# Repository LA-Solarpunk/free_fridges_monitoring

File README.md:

# Free Fridge Monitoring

The city of LA has a network of [free community fridges](https://www.lacommunityfridges.com/)
that serve as distributed food pantries for the city. The [K-Town fridge](https://www.lacommunityfridges.com/fridge/koreatown-solar/r/recZlfyUDA3hGEN5D) is a solar powered version. We're working with
the solar fridge group to build a remote monitoring system for them.

A cloudy week or a door left ajar can spoil everything inside before anyone
notices. This system reports temperature, door state, and battery charge from each
fridge to a central server.

## How it works

A Raspberry Pi at each fridge reads its sensors and publishes a JSON reading once a
minute over MQTT. The Pi reaches the server over Tailscale, so no fridge needs a public
IP or a port forward.

```
Fridge Pi ──> MQTT over Tailscale──> Mosquitto ──> Telegraf ──> InfluxDB
```

Mosquitto is the broker. Telegraf subscribes to `fridges/sensor_data`, parses the JSON,
and writes points into the `freefridges` bucket in InfluxDB. Each fridge has its own
broker account and ACL entry, so a stolen Pi can only publish as itself.

There is a second topic, `fridges/alerts`, that fridges are permitted to write to.
Nothing consumes it yet.

## Server setup

See [ServerConfig/README.md](ServerConfig/README.md). That covers Tailscale, the three
services, and adding a broker account for a new fridge.

## Fridge setup

### 1. Operating system

Flash Raspberry Pi OS 32-bit to a Pi Zero W.

### 2. Enable 1-Wire and serial

Add both temperature bus overlays to `/boot/firmware/config.txt`:

```
dtoverlay=w1-gpio,gpiopin=5
dtoverlay=w1-gpio,gpiopin=6
```

Order matters. The client maps bus masters to GPIO pins by their sorted order on the
filesystem, so pin 5 has to be declared first.

Then run `sudo raspi-config`, go to Interface Options, and enable the serial port
hardware while leaving the serial login shell disabled. The charge controller needs the
UART, and a login shell on it will conflict.

Reboot.

### 3. Tailscale

```bash
curl -fsSL https://tailscale.com/install.sh | sh
sudo tailscale up
```

Ask a Tailscale admin to apply the `fridge` tag to the device.

### 4. Install the client

```bash
git clone https://github.com/LA-Solarpunk/free_fridges_monitoring.git ~/monitoringsystem
cd ~/monitoringsystem/Software
python -m venv venv
./venv/bin/pip install -r Client/requirements.txt
```

### 5. Configure

The client reads its settings from environment variables. Create `/home/pi/fridge.env`:

```
FRIDGE_DEVICE_ID=<fridge name>
MQTT_BROKER=<server tailscale hostname>
MQTT_PORT=1883
MQTT_TOPIC=fridges/sensor_data
MQTT_USERNAME=<fridge broker user>
MQTT_PASSWORD=<fridge broker password>
FRIDGE_LOGLEVEL=INFO
AIRTABLE_API_KEY=unused
FRIDGE_GDRIVE_CREDENTIALS=unused
```

`FRIDGE_DEVICE_ID` is also used as the MQTT client ID, so it has to be unique across
fridges. The broker credentials come from step 7 of the server setup.

The last two variables are required by the config loader even though nothing in the
current data path reads them. See Known gaps below.

Lock the file down, since it holds the broker password:

```bash
chmod 600 /home/pi/fridge.env
```

### 6. Install the service

```bash
sudo cp ~/monitoringsystem/Software/fridge-monitor.service /etc/systemd/system/
sudo systemctl daemon-reload
sudo systemctl enable --now fridge-monitor
```

### 7. Verify

```bash
journalctl -u fridge-monitor -f
```

The client logs each reading before publishing it. If temperatures come back as errors,
check that both W1 bus masters appeared:

```bash
ls /sys/bus/w1/devices/
```

You should see two `w1_bus_master*` entries and a `28-*` entry per probe. If the charge
controller reports no response, the client scans the Modbus address range at startup and
logs what it finds, so the log will say whether it saw the device at all.

Confirm the reading reached the server by querying InfluxDB there.

## Known gaps

**The TOML config is not wired up.** `Client/client.example.toml` and the `SPF_CONFIG`
path helper in `config.py` describe a file-based config that `load_settings()` does not
use. It reads environment variables instead, and every one is a bare lookup with no
default, so a missing variable is a startup crash rather than a warning. Moving to the
TOML file is an open task.

**Airtable and Google Drive are legacy.** `airtable.py` and `google_drive.py` predate
the MQTT pipeline and are no longer imported by `monitor_client.py`. Their config
variables are still required at startup, which is why the env file above sets them to
dummy values.

**The JSON field names came from Airtable.** Keys look like
`Fridge Temperature (°C)`, and `Fridge` is a single-element list rather than a string.
Telegraf flattens these into InfluxDB field names as they are, spaces and degree signs
included, which makes queries awkward. Renaming them means changing `messages.py` and
migrating the existing data.

**Nothing alerts yet.** Sensor data lands in InfluxDB and stops there. Alerting logic,
the shock sensor, the H2 sensor for SLA battery installs, and the audible alarm are all
still unselected or unwritten.

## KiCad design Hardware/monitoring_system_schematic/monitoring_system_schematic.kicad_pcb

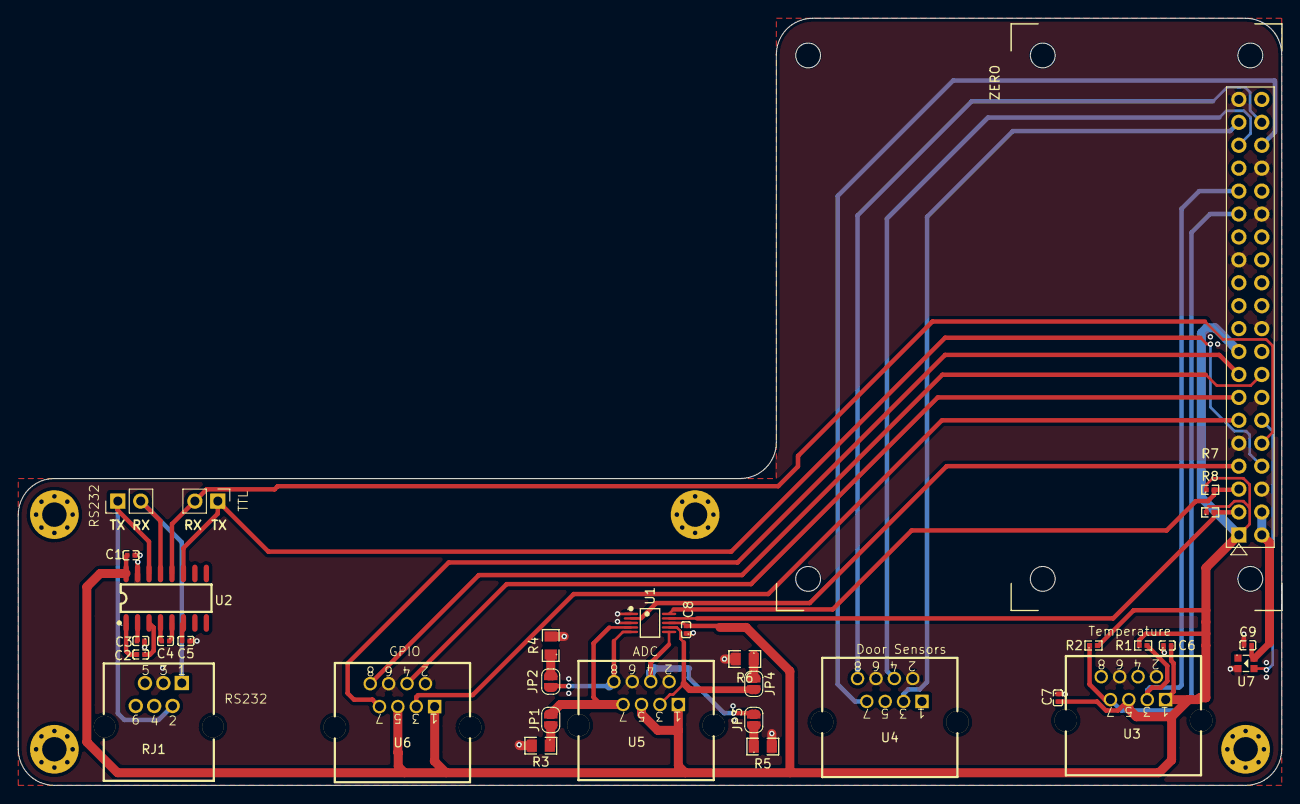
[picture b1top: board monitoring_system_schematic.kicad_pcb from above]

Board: 4 copper layers, 140.0 x 85.0 mm, 36 parts (0 on the bottom side), 35 nets.

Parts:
C1, C2, C3, C4, C5, C6, C7, C8, C9: 0.1u; C307331_C0402
H1, H2, H3, H4: MountingHole; MountingHole_2.7mm_M2.5_Pad_Via
J1: RaspberryPi_GPIO_40W; RPi_Zero_ModelB_40W_Carrier
J2, J3: Conn_01x02; PinHeader_1x02_P2.54mm_Vertical
JP1, JP2, JP3, JP4: SldJmp; SolderJumper-2_P1.3mm_Open_RoundedPad1.0x1.5mm
R1, R2, R7, R8: 4.7k; C25900_R0402
R3, R4, R5, R6: 165; C706217_R0805
RJ1: PCB-6P6C-90_C189747; C189747_RJ11-TH_PCB-6P6C-90
U1: ADS1115; C37593_MSOP-10_L3_0-W3_0-P0_50-LS5_0-BL
U2: MAX3232CDR-JSM; C46596312_SOIC-16_L9_9-W3_9-P1_27-LS6_1-BL
U3, U4, U5, U6: 5501-88011111; C3097726_RJ45-TH_FRJ45017-1100G1K0200
U7: XL-0807RGBC-WS2812B; C3646929_LED-SMD_4P-L2_0-W1_8_XL-0807RGBC-WS2812B

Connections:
3V3: C1.2, C6.2, C7.2, C8.2, J1.1 (3V3), J1.17 (3V3), R1.1, R2.2, R7.1, R8.1, U1.8 (VDD), U2.16 (VCC), U3.1, U3.5, U5.1, U5.5, U6.1, U6.5
5V: C9.2, J1.2 (5V), J1.4 (5V), U7.4 (VDD)
/ADC_ALERT: J1.7 (GPIO4/GPCLK0), U1.2 (ALERT/RDY)
/AIN0: JP1.2 (B), U1.4 (AIN0), U5.7
/AIN1: JP2.2 (B), U1.5 (AIN1), U5.8
/AIN2: JP3.2 (B), U1.6 (AIN2), U5.4
/AIN3: JP4.2 (B), U1.7 (AIN3), U5.3
/FREEZER_NC: J1.38 (GPIO20/MOSI1), U4.8
/FREEZER_NO: J1.36 (GPIO16), U4.7
/FRIDGE_NC: J1.35 (GPIO19/MISO1), U4.4
/FRIDGE_NO: J1.37 (GPIO26), U4.3
/GPIO0: J1.11 (GPIO17), U6.3
/GPIO1: J1.13 (GPIO27), U6.4
/GPIO2: J1.15 (GPIO22), U6.7
/GPIO3: J1.16 (GPIO23), U6.8
/SCL: J1.5 (GPIO3/SCL1), R7.2, U1.10 (SCL)
/SDA: J1.3 (GPIO2/SDA1), R8.2, U1.9 (SDA)
FREEZER_TEMP: J1.29 (GPIO5), R2.1, U3.7
FRIDGE_TEMP: J1.31 (GPIO6), R1.2, U3.3
GND: C1.1, C3.1, C5.1, C6.1, C7.1, C8.1, C9.1, J1.6 (GND), J1.9 (GND), J1.14 (GND), J1.20 (GND), J1.25 (GND), J1.30 (GND), J1.34 (GND), J1.39 (GND), R3.2, R4.2, R5.2, R6.2, RJ1.3, U1.1 (ADDR), U1.3 (GND), U2.15 (GND), U3.2, U3.6, U4.2, U4.6, U5.2, U5.6, U6.2, U6.6, U7.2 (GND)
unnamed: J1.12 (GPIO18/PWM0), U7.3 (DIN)
unnamed: J2.1, RJ1.2, U2.14 (DOUT1)
unnamed: J2.2, RJ1.1, U2.13 (RIN1)
unnamed: JP1.1 (A), R3.1
unnamed: JP2.1 (A), R4.1
unnamed: JP3.1 (A), R5.1
unnamed: JP4.1 (A), R6.1
unnamed: C2.2, U2.1 (C1+)
unnamed: C2.1, U2.3 (C1-)
unnamed: C4.2, U2.4 (C2+)
unnamed: C4.1, U2.5 (C2-)
unnamed: C3.2, U2.2 (V+)
unnamed: C5.2, U2.6 (V-)
RX: J1.10 (GPIO15/RXD0), J3.2, U2.12 (ROUT1)
TX: J1.8 (GPIO14/TXD0), J3.1, U2.11 (DIN1)

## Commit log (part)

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2025-09-17 Configure Secret Detection in `.gitlab-ci.yml`, creating this file if it does not already exist
2025-10-05 Initial test pushing data to airtable
2025-10-06 Added gitignore, updated README, created initial dummy version of airtable posting with real temperature data from DS18B20
2025-10-13 Added google drive API to save file to drive. Added airtable fetch function to pull CSV values for given fridge from airtable. Updated README to reflect google drive setup.
2025-10-13 Fixed airtable.py fridge ID printing functionality
2025-10-13 Fixed potential logging issue for months with 31 days, added function to get the fridge name
2025-10-13 Added schedule save to drive
2025-10-13 Renamed door file to include both types of sensors. Added code to actually read state.
2025-10-14 Added RPi.GPIO to requirements. Fixed magnet sensor setup. Updated readme to reflect that token.json can be theoretically re-used.
2025-10-17 Updated airtable to properly represent error state of fridge door
2025-10-17 Added basic charge interface with address check
2025-10-19 Fixed some issues with the charge interface handling when there are connection issues. Added an error column to airtable.
2025-10-19 Fixed bug in airtable data conversion for door sensor, added some basic integration tests
2025-11-11 Untested addition of mqtt
2025-11-11 Moving to separate client folder for future client/server management
2025-11-11 added config to manage secrets and settings
2026-04-03 Updating temp interface
2026-04-16 Added some integration tests and updated temp interface for multiple sensors
2026-04-17 Got mqtt working end to end, cleaned up config to use env variables, and minor tweaks to messages to streamline into main system
2026-04-17 Updated to include fridge data
2026-04-19 Added functionality to check for broken pins on the magnet sensors
2026-05-03 Added sensor reading type to capture data and errors
2026-05-05 Fixed bug in door monitoring code, added sysd service definition
